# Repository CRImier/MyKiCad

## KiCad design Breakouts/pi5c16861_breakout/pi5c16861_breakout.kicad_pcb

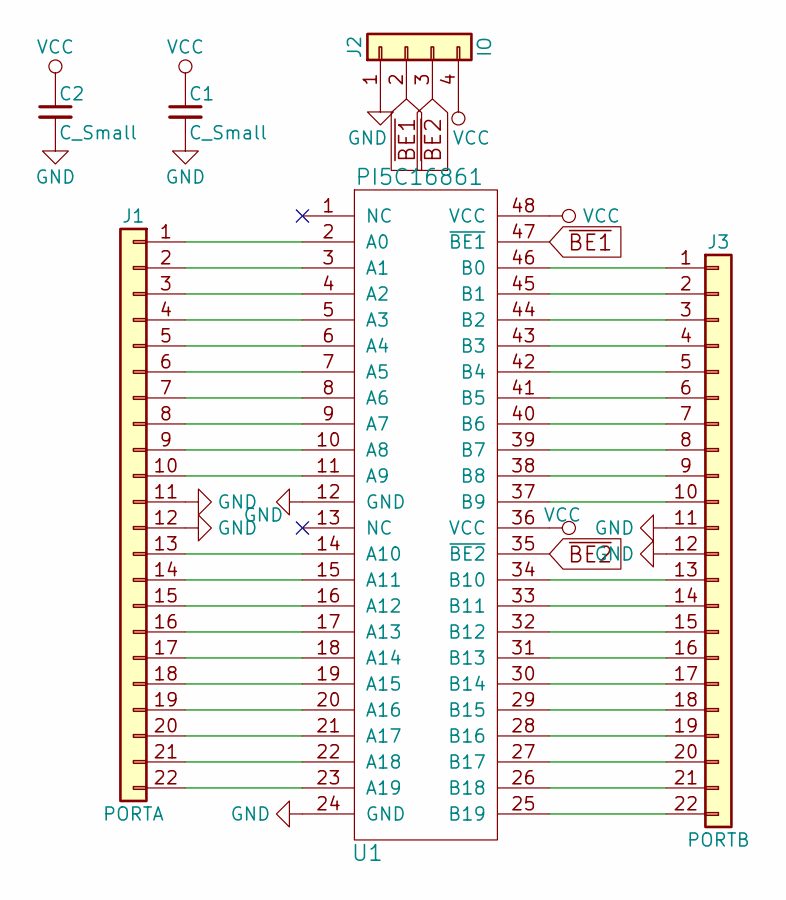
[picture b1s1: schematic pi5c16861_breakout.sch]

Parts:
C1, C2: C_Small; C_0402
J1: PORTA; Pin_Header_Straight_2x11_Pitch2.00mm
J2: IO; Pin_Header_Straight_1x04_Pitch2.54mm
J3: PORTB; Pin_Header_Straight_2x11_Pitch2.00mm
U1: PI5C16861; BSQOP48

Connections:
GND: C1.2, C2.2, J1.11, J1.12, J2.1, J3.11, J3.12, U1.12 (GND), U1.24 (GND)
unnamed: J1.1, U1.2 (A0)
unnamed: J1.2, U1.3 (A1)
unnamed: J1.3, U1.4 (A2)
unnamed: J1.4, U1.5 (A3)
unnamed: J1.5, U1.6 (A4)
unnamed: J1.6, U1.7 (A5)
unnamed: J1.7, U1.8 (A6)
unnamed: J1.8, U1.9 (A7)
unnamed: J1.9, U1.10 (A8)
unnamed: J1.10, U1.11 (A9)
unnamed: J1.13, U1.14 (A10)
unnamed: J1.14, U1.15 (A11)
unnamed: J1.15, U1.16 (A12)
unnamed: J1.16, U1.17 (A13)
unnamed: J1.17, U1.18 (A14)
unnamed: J1.18, U1.19 (A15)
unnamed: J1.19, U1.20 (A16)
unnamed: J1.20, U1.21 (A17)
unnamed: J1.21, U1.22 (A18)
unnamed: J1.22, U1.23 (A19)
unnamed: J3.1, U1.46 (B0)
unnamed: J3.2, U1.45 (B1)
unnamed: J3.3, U1.44 (B2)
unnamed: J3.4, U1.43 (B3)
unnamed: J3.5, U1.42 (B4)
unnamed: J3.6, U1.41 (B5)
unnamed: J3.7, U1.40 (B6)
unnamed: J3.8, U1.39 (B7)
unnamed: J3.9, U1.38 (B8)
unnamed: J3.10, U1.37 (B9)
unnamed: J3.13, U1.34 (B10)
unnamed: J3.14, U1.33 (B11)
unnamed: J3.15, U1.32 (B12)
unnamed: J3.16, U1.31 (B13)
unnamed: J3.17, U1.30 (B14)
unnamed: J3.18, U1.29 (B15)
unnamed: J3.19, U1.28 (B16)
unnamed: J3.20, U1.27 (B17)
unnamed: J3.21, U1.26 (B18)
unnamed: J3.22, U1.25 (B19)
VCC: C1.1, C2.1, J2.4, U1.36 (VCC), U1.48 (VCC)
~BE1: J2.2, U1.47 (~BE1)
~BE2: J2.3, U1.35 (~BE2)

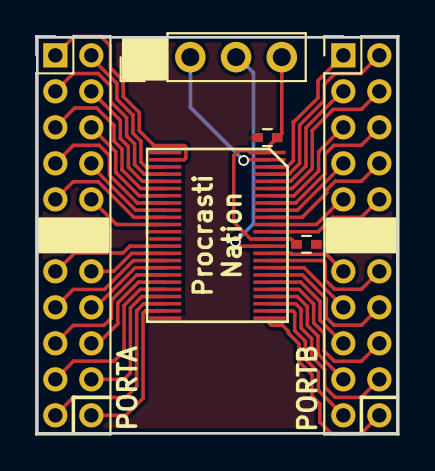
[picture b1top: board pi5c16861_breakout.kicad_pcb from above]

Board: 2 copper layers, 20.0 x 22.0 mm, 6 parts (0 on the bottom side), 44 nets.

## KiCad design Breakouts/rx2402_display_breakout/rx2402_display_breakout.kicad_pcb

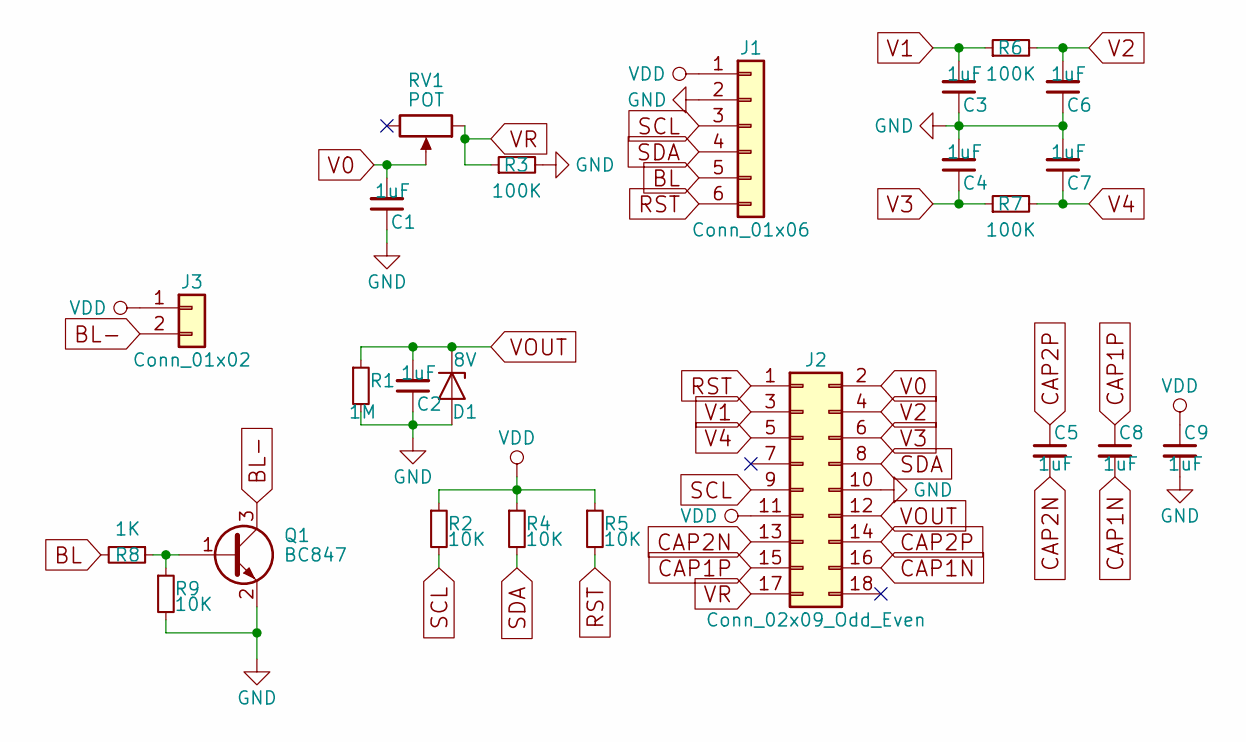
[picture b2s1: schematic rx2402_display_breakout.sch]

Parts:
C1, C2, C3, C4, C5, C6, C7, C8, C9: 1uF; C_0603_HandSoldering
D1: 8V; D_MiniMELF
J1: Conn_01x06; Pin_Header_Straight_1x06_Pitch2.54mm
J2: Conn_02x09_Odd_Even; Pin_Header_Straight_2x09_Pitch2.54mm
J3: Conn_01x02; Pin_Header_Straight_2x01_Pitch2.54mm
Q1: BC847; SOT-23
R1: 1M; R_0603_HandSoldering
R2, R4, R5, R9: 10K; R_0603_HandSoldering
R3, R6, R7: 100K; R_0603_HandSoldering
R8: 1K; R_0603_HandSoldering
RV1: POT; Potentiometer_Trimmer_ACP_CA6v_Horizontal

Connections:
BL: J1.5, R8.2
BL-: J3.2, Q1.3 (C)
CAP1N: C8.2, J2.16
CAP1P: C8.1, J2.15
CAP2N: C5.2, J2.13
CAP2P: C5.1, J2.14
GND: C1.1, C2.1, C3.1, C4.2, C6.1, C7.2, C9.2, D1.2 (A), J1.2, J2.10, Q1.2 (E), R1.2, R3.2, R9.2
unnamed: Q1.1 (B), R8.1, R9.1
RST: J1.6, J2.1, R5.2
SCL: J1.3, J2.9, R2.2
SDA: J1.4, J2.8, R4.2
V0: C1.2, J2.2, RV1.2
V1: C3.2, J2.3, R6.1
V2: C6.2, J2.4, R6.2
V3: C4.1, J2.6, R7.1
V4: C7.1, J2.5, R7.2
VDD: C9.1, J1.1, J2.11, J3.1, R2.1, R4.1, R5.1
VOUT: C2.2, D1.1 (K), J2.12, R1.1
VR: J2.17, R3.1, RV1.1

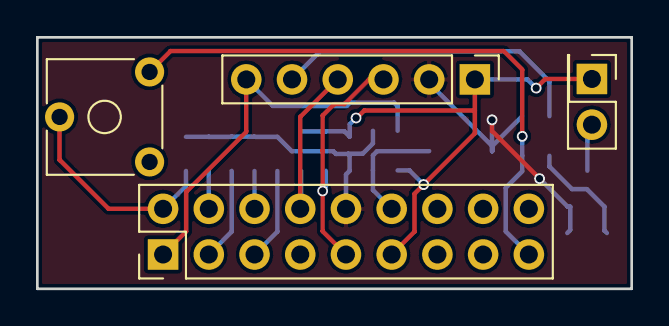
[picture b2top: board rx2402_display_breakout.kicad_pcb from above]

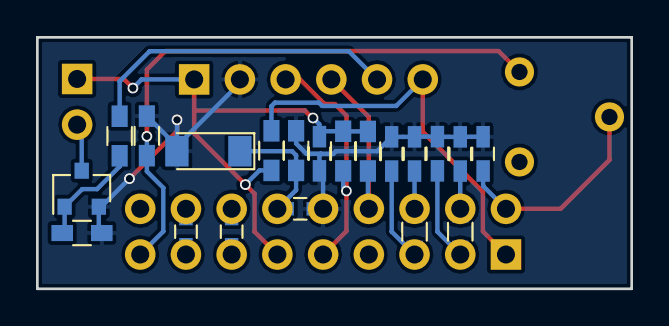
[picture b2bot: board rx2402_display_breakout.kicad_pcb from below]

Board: 2 copper layers, 33.0 x 14.0 mm, 24 parts (20 on the bottom side), 19 nets.

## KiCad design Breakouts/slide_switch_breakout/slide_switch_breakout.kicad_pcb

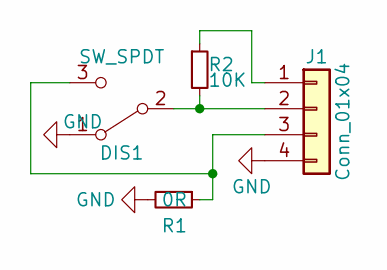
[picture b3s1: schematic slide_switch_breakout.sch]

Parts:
DIS1: SW_SPDT; SW_SPDT_PCM12
J1: Conn_01x04; Pin_Header_Straight_1x04_Pitch2.54mm
R1: 0R; R_0402
R2: 10K; R_0402

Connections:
GND: DIS1.1 (A), J1.4, R1.2
unnamed: DIS1.2 (B), J1.2, R2.2
unnamed: DIS1.3 (C), J1.3, R1.1
unnamed: J1.1, R2.1

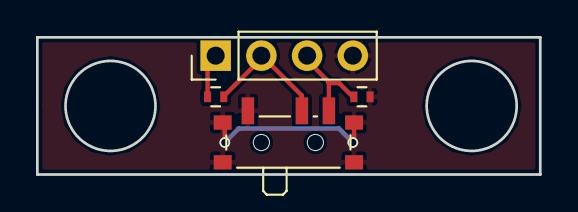
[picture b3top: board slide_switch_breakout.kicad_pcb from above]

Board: 2 copper layers, 27.9 x 7.6 mm, 4 parts (0 on the bottom side), 4 nets.

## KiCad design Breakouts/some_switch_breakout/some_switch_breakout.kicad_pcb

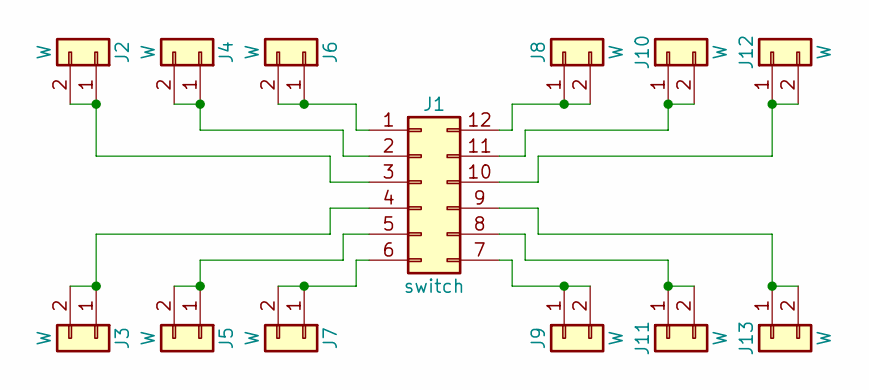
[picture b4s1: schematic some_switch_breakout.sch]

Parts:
J1: switch; SOME_SWITCH
J2, J3, J4, J5, J6, J7, J8, J9, J10, J11, J12, J13: W; WireConnection_2.00mmDrill

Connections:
unnamed: J1.1, J6.1, J6.2
unnamed: J1.2, J4.1, J4.2
unnamed: J1.3, J2.1, J2.2
unnamed: J1.4, J3.1, J3.2
unnamed: J1.5, J5.1, J5.2
unnamed: J1.6, J7.1, J7.2
unnamed: J1.7, J9.1, J9.2
unnamed: J1.8, J11.1, J11.2
unnamed: J1.9, J13.1, J13.2
unnamed: J1.10, J12.1, J12.2
unnamed: J1.11, J10.1, J10.2
unnamed: J1.12, J8.1, J8.2

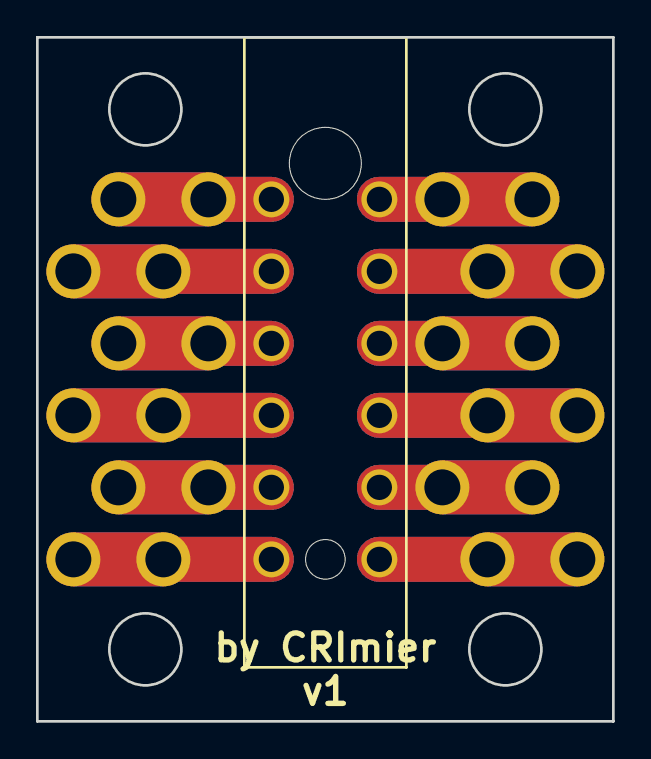
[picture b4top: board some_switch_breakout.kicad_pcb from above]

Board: 2 copper layers, 32.0 x 38.0 mm, 13 parts (0 on the bottom side), 12 nets.

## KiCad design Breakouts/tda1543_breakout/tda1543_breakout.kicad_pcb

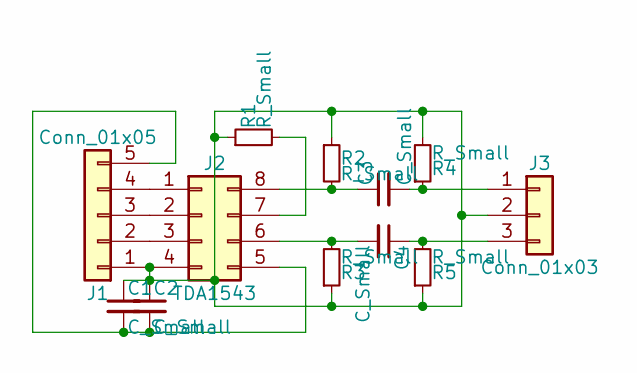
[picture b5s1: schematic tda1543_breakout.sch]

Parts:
C1, C2: C_Small; C_0805_HandSoldering
C3, C4: C_Small; C_1206_HandSoldering
J1: Conn_01x05; Pin_Header_Straight_1x05_Pitch2.54mm
J2: TDA1543; DIP-8_W7.62mm
J3: Conn_01x03; Pin_Header_Straight_1x03_Pitch2.54mm
R1: R_Small; Pin_Header_Straight_1x02_Pitch2.54mm
R2, R3, R4, R5: R_Small; R_0603_HandSoldering

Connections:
unnamed: C1.1, C2.1, J1.1, J2.4, J3.2, R1.1, R2.1, R3.1, R4.2, R5.1
unnamed: C1.2, C2.2, J1.5, J2.5
unnamed: C3.1, J2.8, R2.2
unnamed: C3.2, J3.1, R4.1
unnamed: C4.1, J3.3, R5.2
unnamed: C4.2, J2.6, R3.2
unnamed: J1.2, J2.3
unnamed: J1.3, J2.2
unnamed: J1.4, J2.1
unnamed: J2.7, R1.2

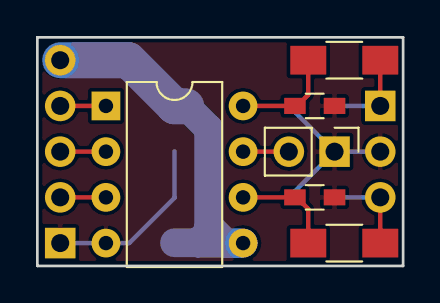
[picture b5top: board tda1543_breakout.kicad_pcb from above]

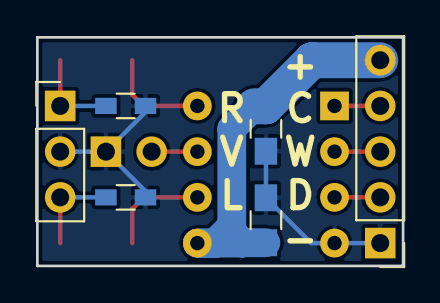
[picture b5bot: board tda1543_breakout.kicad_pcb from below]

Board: 2 copper layers, 20.3 x 12.7 mm, 12 parts (6 on the bottom side), 10 nets.

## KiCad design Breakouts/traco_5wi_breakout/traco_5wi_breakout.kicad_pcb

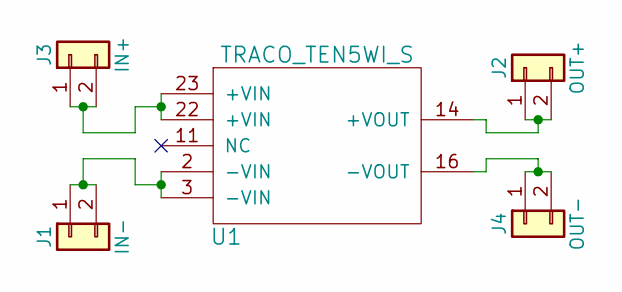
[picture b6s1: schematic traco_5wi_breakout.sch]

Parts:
J1: IN-; WireConnection_2.00mmDrill
J2: OUT+; WireConnection_2.00mmDrill
J3: IN+; WireConnection_2.00mmDrill
J4: OUT-; WireConnection_2.00mmDrill
U1: TRACO_TEN5WI_S; TRACO_TEN_5WI_S

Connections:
unnamed: J1.1, J1.2, U1.2 (-VIN), U1.3 (-VIN)
unnamed: J2.1, J2.2, U1.14 (+VOUT)
unnamed: J3.1, J3.2, U1.22 (+VIN), U1.23 (+VIN)
unnamed: J4.1, J4.2, U1.16 (-VOUT)

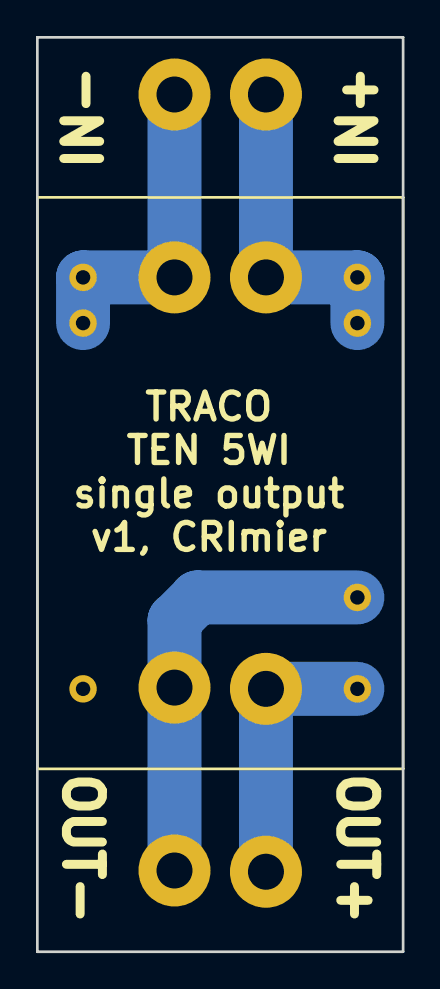
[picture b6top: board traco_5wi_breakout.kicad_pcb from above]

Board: 2 copper layers, 20.3 x 50.8 mm, 5 parts (0 on the bottom side), 4 nets.

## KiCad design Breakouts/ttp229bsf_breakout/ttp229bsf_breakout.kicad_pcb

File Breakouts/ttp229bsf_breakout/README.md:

# TTP229BSF breakout board

A heart-shaped breakout for the TTP229BSF 16-channel capacitative touch controller IC.
Is designed for SaferSpace project - a collection of tools ensuring physical safety of a hackerspace.
The sensitivity adjustment capacitor values aren't yet selected - will probably use a Chinese TTP229BSF breakout
as a reference for selecting those capacitors' values when these PCBs arrive.
Each pair of touch pins has a 4-channel low-capacity ESD diode assembly, with 2 diodes per every pin for extra protection.
VCC on the diode assemblies is left unconnected but is connect-able to main VCC using jumper wires if necessary.
The bottom side has footprints for resistors that can be used for TTP229BSF configuration.

VCC, GND, SCK and SDO are exposed on a 4-pin header - no silkscreened pinout, but do check the board files.
There's a groundplane under the ICs, but not under the testpoints and the ESD diodes.
Testpoint names are silkscreened on the board top layer.

- PCB size:  61.8 mm* 51.9 mm 
- Layer count: 2
- Recommended thickness: 1.6mm (the board was tested to work well with 1.6mm, and future mechanical integrations will assume 1.6mm too)

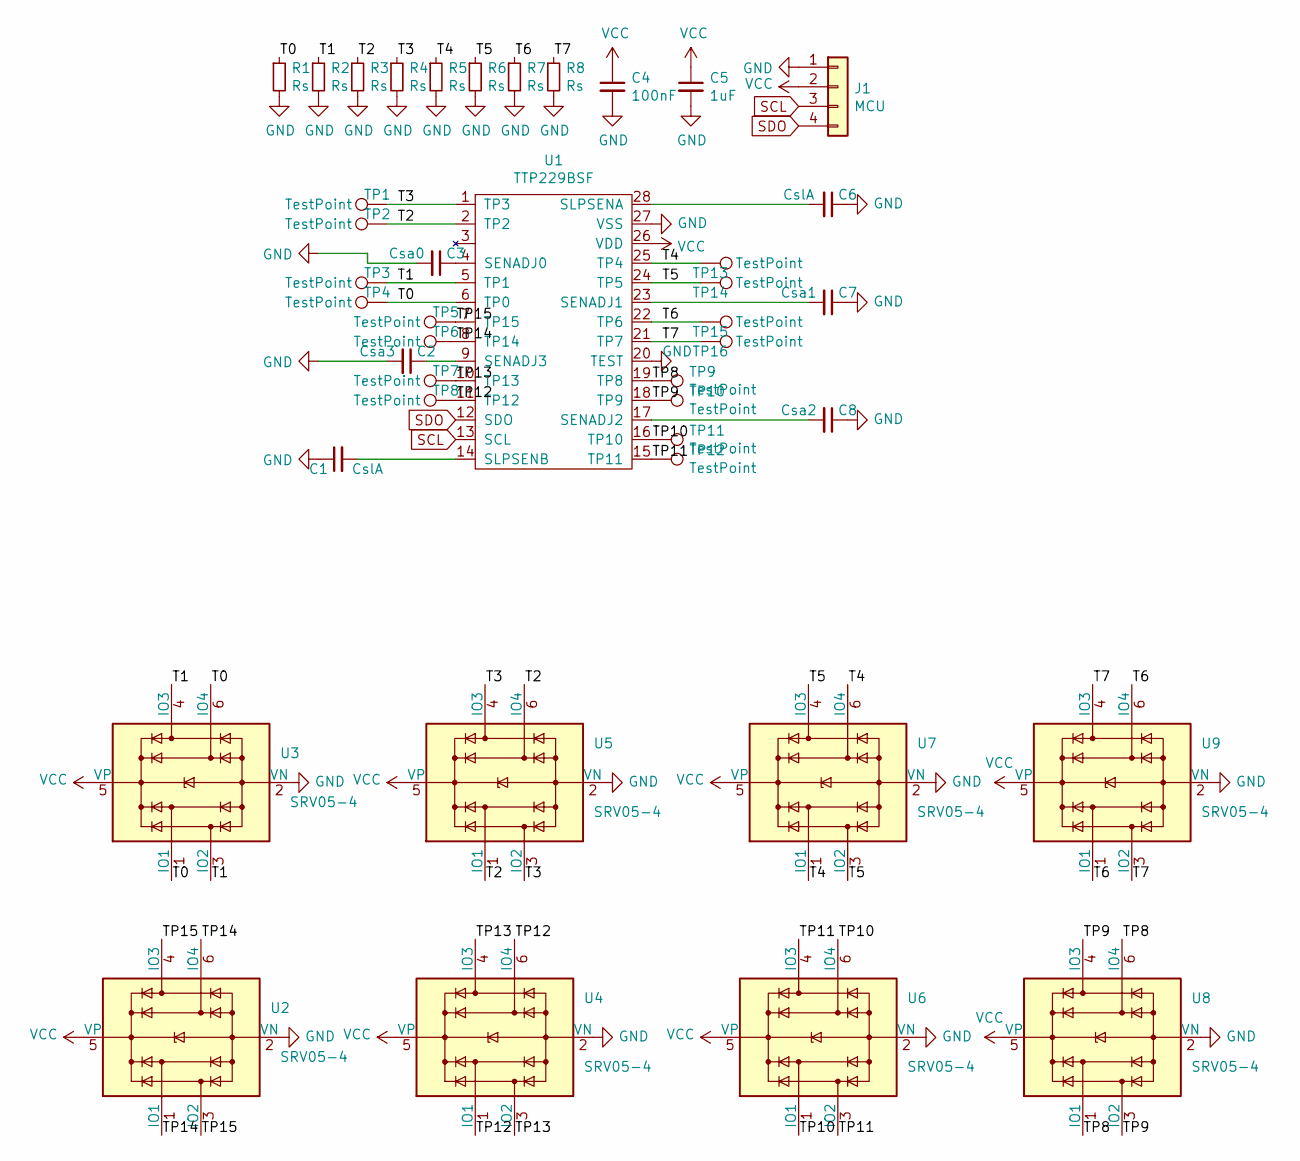
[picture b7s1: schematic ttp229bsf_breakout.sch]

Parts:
C1, C6: CslA; C_0805_2012Metric_Pad1.15x1.40mm_HandSolder
C2: Csa3; C_0805_2012Metric_Pad1.15x1.40mm_HandSolder
C3: Csa0; C_0805_2012Metric_Pad1.15x1.40mm_HandSolder
C4: 100nF; C_0805_2012Metric_Pad1.15x1.40mm_HandSolder
C5: 1uF; C_0805_2012Metric_Pad1.15x1.40mm_HandSolder
C7: Csa1; C_0805_2012Metric_Pad1.15x1.40mm_HandSolder
C8: Csa2; C_0805_2012Metric_Pad1.15x1.40mm_HandSolder
J1: MCU; PinHeader_1x04_P2.54mm_Vertical
R1, R2, R3, R4, R5, R6, R7, R8: Rs; R_0805_2012Metric_Pad1.15x1.40mm_HandSolder
TP1, TP2, TP3, TP4, TP5, TP6, TP7, TP8, TP9, TP10, TP11, TP12, TP13, TP14, TP15, TP16: TestPoint; TestPoint_Pad_D4.0mm
U1: TTP229BSF; SSOP-28_3.9x9.9mm_P0.635mm
U2, U3, U4, U5, U6, U7, U8, U9: SRV05-4; SOT-23-6

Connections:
/T0: R1.1, TP4.1, U1.6 (TP0), U3.1 (IO1), U3.6 (IO4)
/T1: R2.1, TP3.1, U1.5 (TP1), U3.3 (IO2), U3.4 (IO3)
/T2: R3.1, TP2.1, U1.2 (TP2), U5.1 (IO1), U5.6 (IO4)
/T3: R4.1, TP1.1, U1.1 (TP3), U5.3 (IO2), U5.4 (IO3)
/T4: R5.1, TP13.1, U1.25 (TP4), U7.1 (IO1), U7.6 (IO4)
/T5: R6.1, TP14.1, U1.24 (TP5), U7.3 (IO2), U7.4 (IO3)
/T6: R7.1, TP15.1, U1.22 (TP6), U9.1 (IO1), U9.6 (IO4)
/T7: R8.1, TP16.1, U1.21 (TP7), U9.3 (IO2), U9.4 (IO3)
/TP8: TP9.1, U1.19 (TP8), U8.1 (IO1), U8.6 (IO4)
/TP9: TP10.1, U1.18 (TP9), U8.3 (IO2), U8.4 (IO3)
/TP10: TP11.1, U1.16 (TP10), U6.1 (IO1), U6.6 (IO4)
/TP11: TP12.1, U1.15 (TP11), U6.3 (IO2), U6.4 (IO3)
/TP12: TP8.1, U1.11 (TP12), U4.1 (IO1), U4.6 (IO4)
/TP13: TP7.1, U1.10 (TP13), U4.3 (IO2), U4.4 (IO3)
/TP14: TP6.1, U1.8 (TP14), U2.1 (IO1), U2.6 (IO4)
/TP15: TP5.1, U1.7 (TP15), U2.3 (IO2), U2.4 (IO3)
GND: C1.1, C2.2, C3.2, C4.2, C5.2, C6.1, C7.1, C8.1, J1.1, R1.2, R2.2, R3.2, R4.2, R5.2, R6.2, R7.2, R8.2, U1.20 (TEST), U1.27 (VSS), U2.2 (VN), U3.2 (VN), U4.2 (VN), U5.2 (VN), U6.2 (VN), U7.2 (VN), U8.2 (VN), U9.2 (VN)
unnamed: C1.2, U1.14 (SLPSENB)
unnamed: C2.1, U1.9 (SENADJ3)
unnamed: C3.1, U1.4 (SENADJ0)
unnamed: C6.2, U1.28 (SLPSENA)
unnamed: C7.2, U1.23 (SENADJ1)
unnamed: C8.2, U1.17 (SENADJ2)
SCL: J1.3, U1.13 (SCL)
SDO: J1.4, U1.12 (SDO)
VCC: C4.1, C5.1, J1.2, U1.26 (VDD), U2.5 (VP), U3.5 (VP), U4.5 (VP), U5.5 (VP), U6.5 (VP), U7.5 (VP), U8.5 (VP), U9.5 (VP)

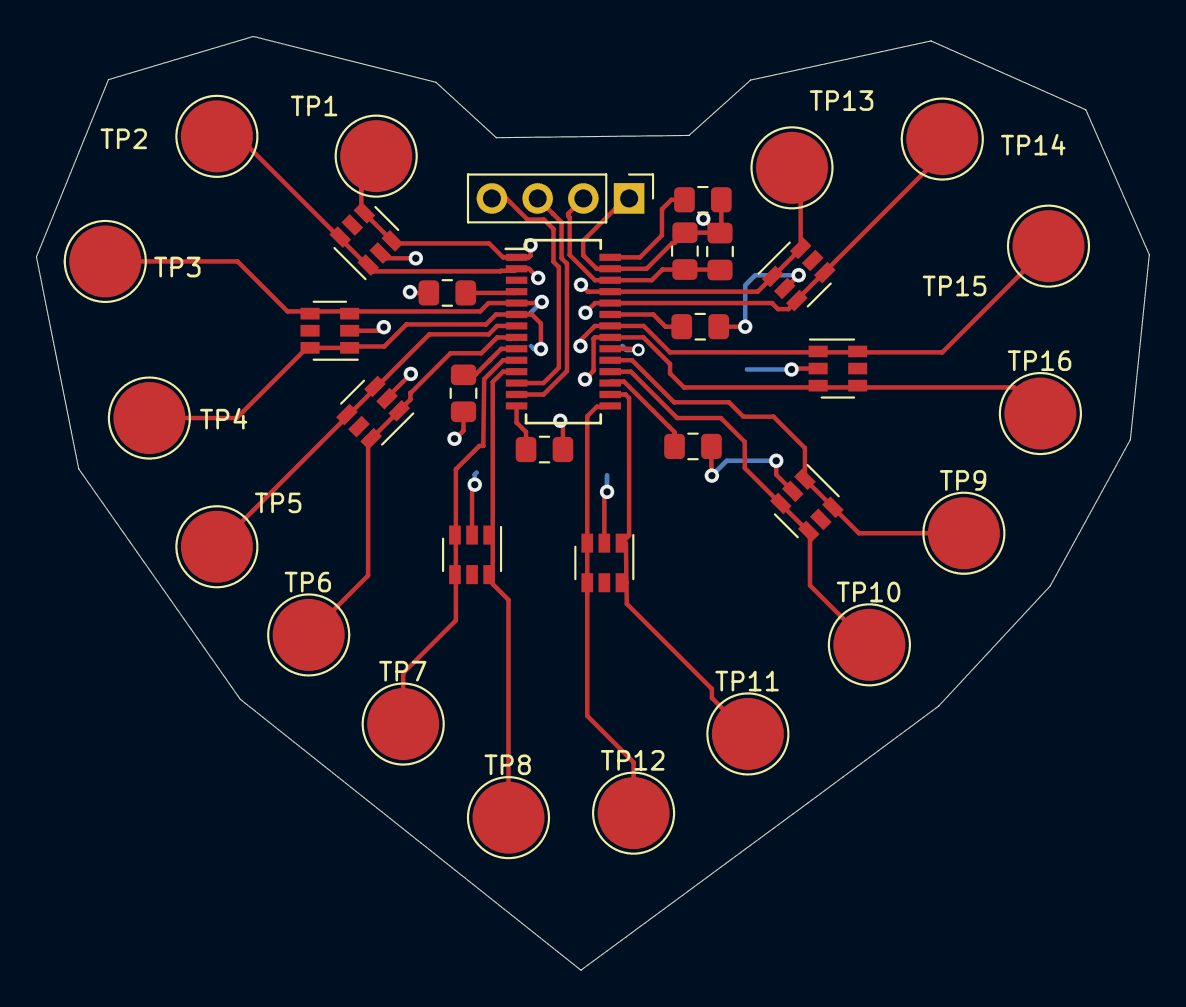
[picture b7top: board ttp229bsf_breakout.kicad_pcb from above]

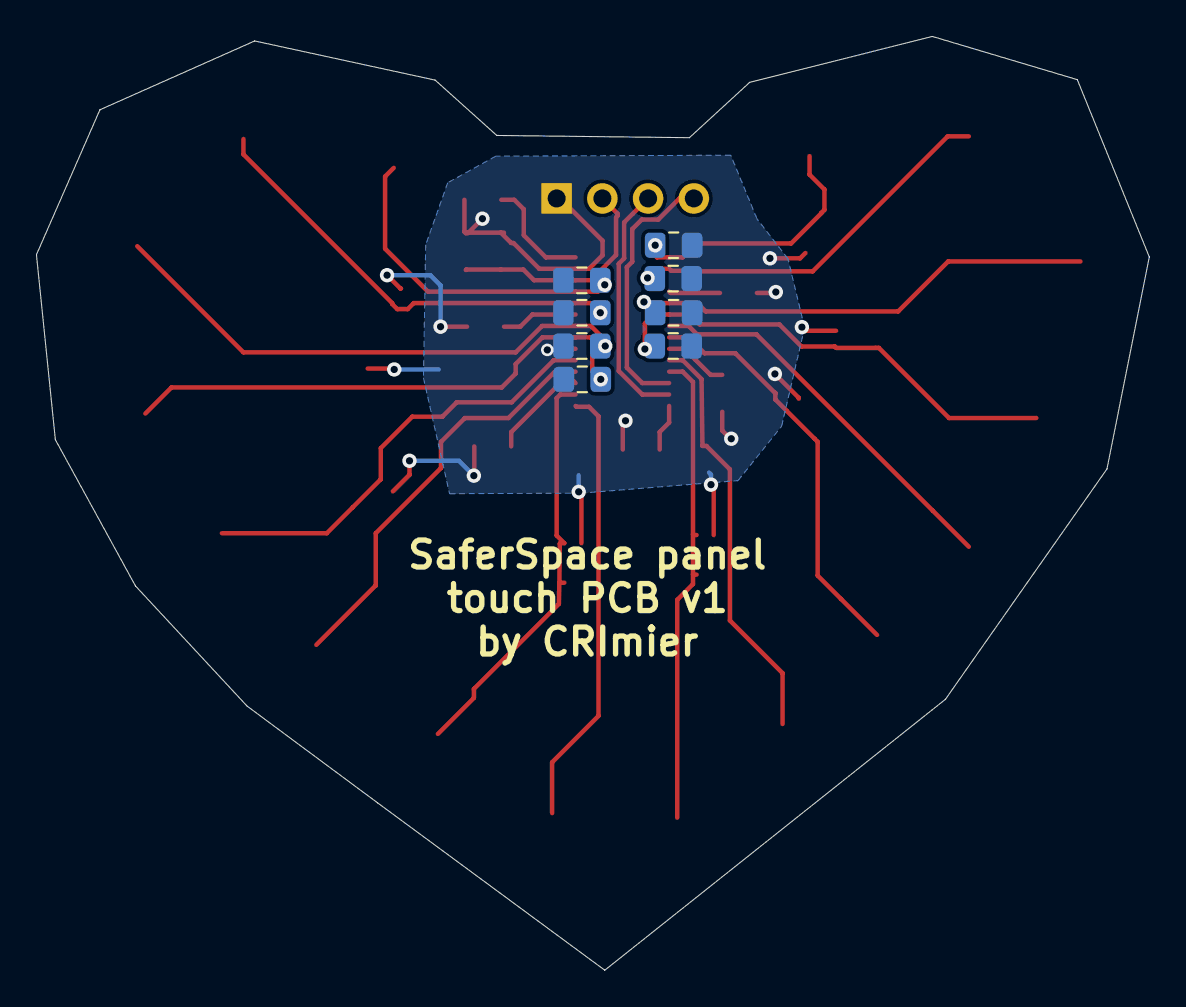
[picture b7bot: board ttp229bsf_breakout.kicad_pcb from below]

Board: 2 copper layers, 61.8 x 51.9 mm, 42 parts (8 on the bottom side), 26 nets.

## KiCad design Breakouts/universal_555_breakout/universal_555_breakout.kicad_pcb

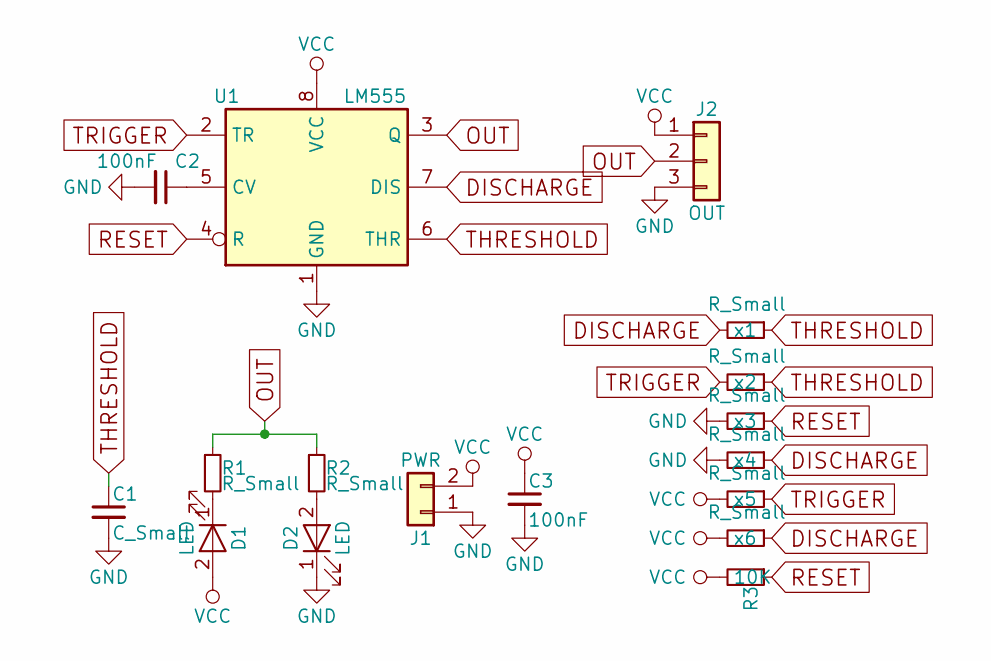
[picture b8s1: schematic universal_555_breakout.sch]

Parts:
C1: C_Small; R_0805_HandSoldering
C2, C3: 100nF; R_0805_HandSoldering
D1, D2: LED; LED_0805_HandSoldering
J1: PWR; Pin_Header_Straight_1x02_Pitch2.54mm
J2: OUT; Pin_Header_Straight_1x03_Pitch2.54mm
R1, R2: R_Small; R_0805_HandSoldering
R3: 10K; R_0805_HandSoldering
U1: LM555; DIP-8_W7.62mm
x1, x2, x3, x4, x5, x6: R_Small; R_0805_HandSoldering

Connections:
DISCHARGE: U1.7 (DIS), x1.2, x4.1, x6.1
GND: C1.2, C2.2, C3.2, D2.1 (K), J1.1, J2.3, U1.1 (GND), x3.2, x4.2
unnamed: C2.1, U1.5 (CV)
unnamed: D1.1 (K), R1.2
unnamed: D2.2 (A), R2.2
OUT: J2.2, R1.1, R2.1, U1.3 (Q)
RESET: R3.1, U1.4 (R), x3.1
THRESHOLD: C1.1, U1.6 (THR), x1.1, x2.1
TRIGGER: U1.2 (TR), x2.2, x5.1
VCC: C3.1, D1.2 (A), J1.2, J2.1, R3.2, U1.8 (VCC), x5.2, x6.2

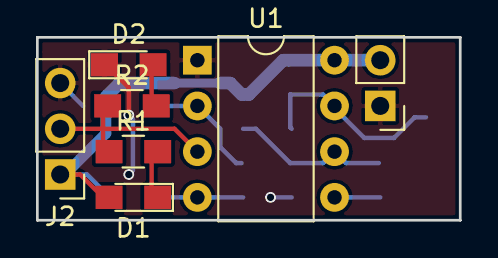
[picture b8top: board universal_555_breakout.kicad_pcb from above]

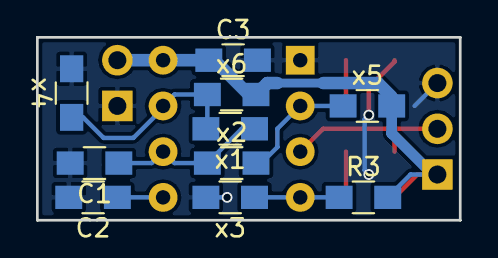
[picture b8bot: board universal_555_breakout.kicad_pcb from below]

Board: 2 copper layers, 23.5 x 10.2 mm, 17 parts (10 on the bottom side), 10 nets.
